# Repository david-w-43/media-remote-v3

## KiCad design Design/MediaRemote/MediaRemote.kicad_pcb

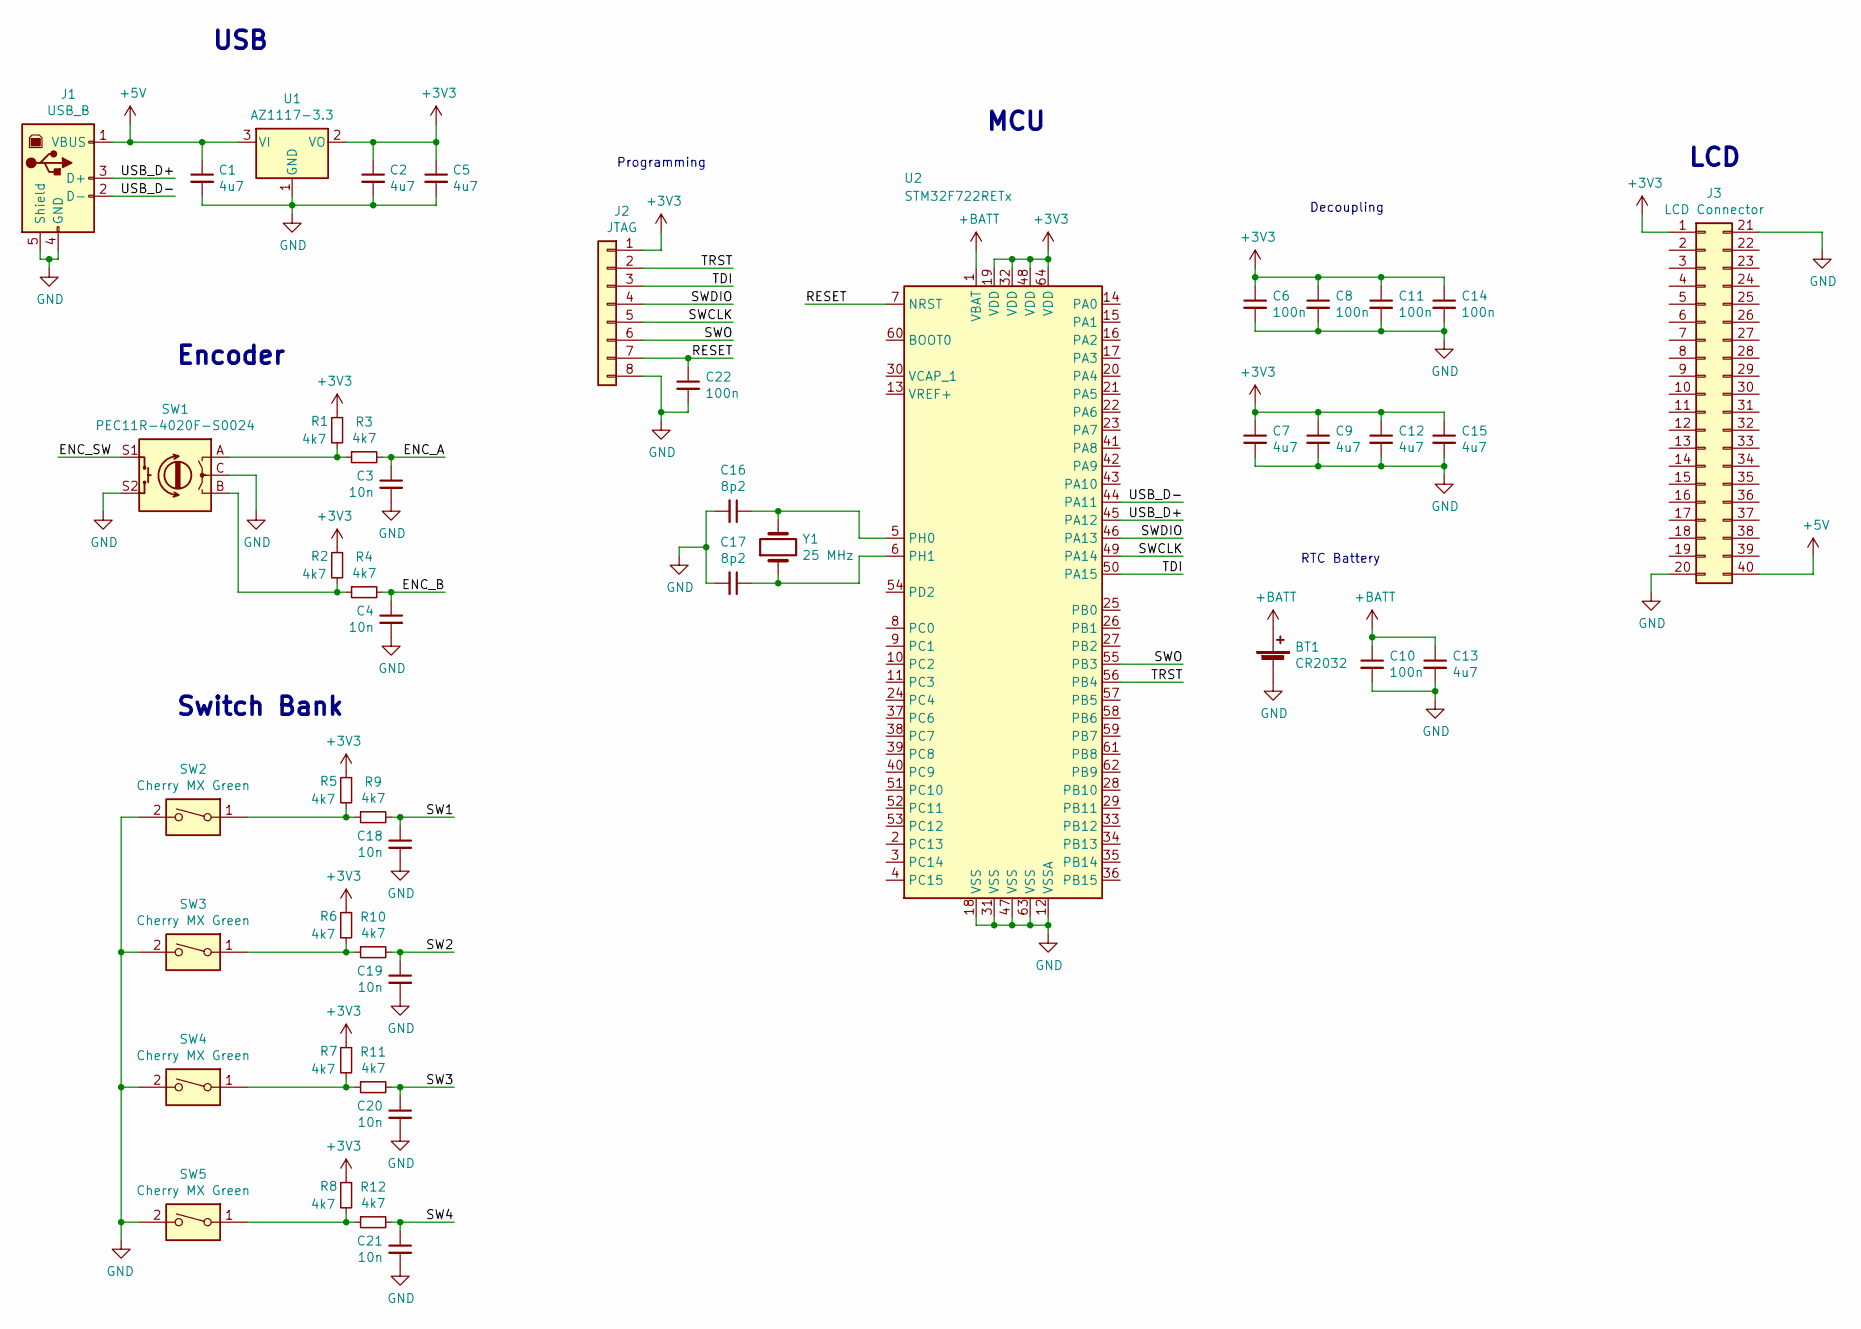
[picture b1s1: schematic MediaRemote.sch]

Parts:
BT1: CR2032; BatteryHolder_Keystone_3002_1x2032
C1, C2, C5, C7, C9, C12, C13, C15: 4u7; C_0805_2012Metric_Pad1.18x1.45mm_HandSolder
C3, C4, C18, C19, C20, C21: 10n; C_0805_2012Metric_Pad1.18x1.45mm_HandSolder
C6, C8, C10, C11, C14, C22: 100n; C_0805_2012Metric_Pad1.18x1.45mm_HandSolder
C16, C17: 8p2; C_0805_2012Metric_Pad1.18x1.45mm_HandSolder
J1: USB_B; USB_B_Lumberg_2411_02_Horizontal
J2: JTAG; PinHeader_1x08_P2.54mm_Vertical
J3: LCD Connector; PinHeader_2x20_P2.54mm_Vertical
R1, R2, R3, R4, R5, R6, R7, R8, R9, R10, R11, R12: 4k7; R_0805_2012Metric_Pad1.20x1.40mm_HandSolder
SW1: PEC11R-4020F-S0024; RotaryEncoder_Alps_EC12E-Switch_Vertical_H20mm
SW2, SW3, SW4, SW5: Cherry MX Green; SW_Cherry_MX_1.00u_Plate
U1: AZ1117-3.3; TO-252-2
U2: STM32F722RETx; LQFP-64_10x10mm_P0.5mm
Y1: 25 MHz; Crystal_HC49-4H_Vertical

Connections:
+3V3: C2.1, C5.1, C6.1, C7.1, C8.1, C9.1, C11.1, C12.1, C14.1, C15.1, J2.1, J3.1, R1.1, R2.1, R5.1, R6.1, R7.1, R8.1, U1.2 (VO), U2.19 (VDD), U2.32 (VDD), U2.48 (VDD), U2.64 (VDD)
+5V: C1.1, J1.1 (VBUS), J3.40, U1.3 (VI)
+BATT: BT1.1 (+), C10.1, C13.1, U2.1 (VBAT)
/ENC_A: C3.1, R3.2
/ENC_B: C4.1, R4.2
/ENC_SW: SW1.S1
/RESET: C22.1, J2.7, U2.7 (NRST)
/SW1: C18.1, R9.2
/SW2: C19.1, R10.2
/SW3: C20.1, R11.2
/SW4: C21.1, R12.2
/SWCLK: J2.5, U2.49 (PA14)
/SWDIO: J2.4, U2.46 (PA13)
/SWO: J2.6, U2.55 (PB3)
/TDI: J2.3, U2.50 (PA15)
/TRST: J2.2, U2.56 (PB4)
/USB_D+: J1.3 (D+), U2.45 (PA12)
/USB_D-: J1.2 (D-), U2.44 (PA11)
GND: BT1.2 (-), C1.2, C2.2, C3.2, C4.2, C5.2, C6.2, C7.2, C8.2, C9.2, C10.2, C11.2, C12.2, C13.2, C14.2, C15.2, C16.2, C17.2, C18.2, C19.2, C20.2, C21.2, C22.2, J1.4 (GND), J1.5 (Shield), J2.8, J3.20, J3.21, SW1.C, SW1.S2, SW2.2, SW3.2, SW4.2, SW5.2, U1.1 (GND), U2.12 (VSSA), U2.18 (VSS), U2.31 (VSS), U2.47 (VSS), U2.63 (VSS)
unnamed: C16.1, U2.5 (PH0), Y1.2
unnamed: C17.1, U2.6 (PH1), Y1.1
unnamed: R1.2, R3.1, SW1.A
unnamed: R2.2, R4.1, SW1.B
unnamed: R5.2, R9.1, SW2.1
unnamed: R6.2, R10.1, SW3.1
unnamed: R7.2, R11.1, SW4.1
unnamed: R8.2, R12.1, SW5.1

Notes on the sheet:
Switch Bank
MCU
Encoder
LCD
Decoupling
RTC Battery
Programming
USB

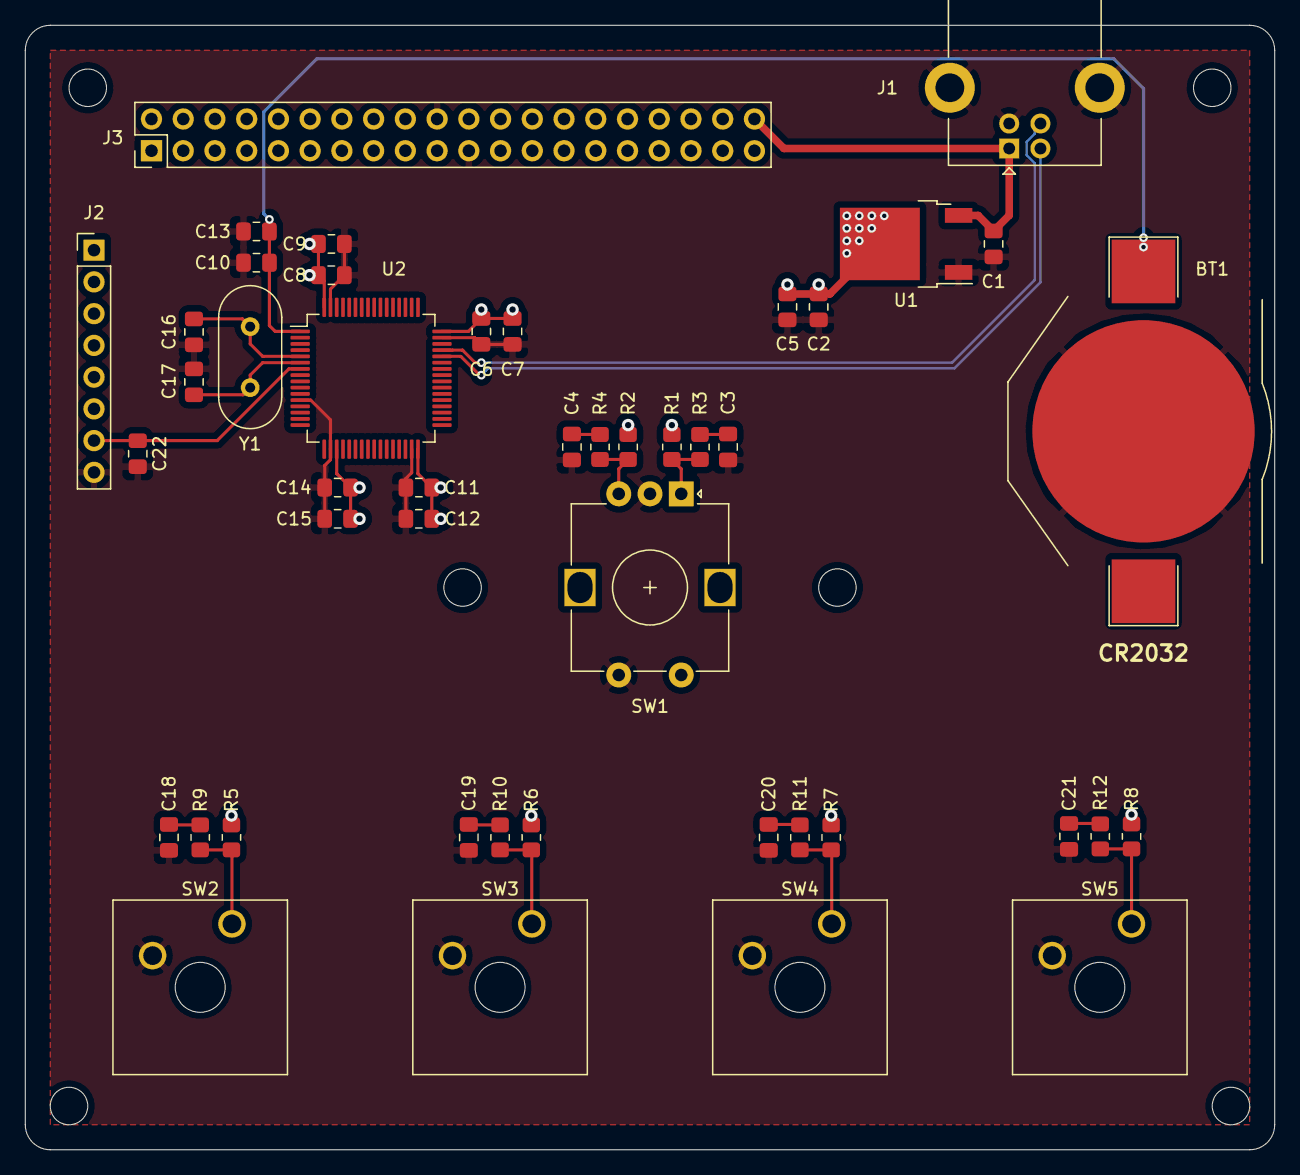
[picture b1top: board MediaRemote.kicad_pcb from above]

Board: 2 copper layers, 100.0 x 90.0 mm, 46 parts (0 on the bottom side), 26 nets.

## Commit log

2021-07-26 Add .gitignore and .gitattributes.
2021-07-26 Add project files.
2021-07-27 Demonstrates Media Application Interface with MEF
2021-07-27 Some basic serial comms methods
2021-07-29 Moved CompanionApplication to new folder, added STM32Cube project
2021-08-02 Added tray icon
2021-08-03 Implemented timer and events to monitor changes
2021-08-04 Release COM object on disconnect
2021-08-04 iTunes member implementations
2021-08-04 Automatically load interfaces into tray icon context menu
2021-08-06 Sets application interface with context menu
2021-08-06 Update .gitattributes
    Exclude stm32 drivers from language stats
2021-08-06 Added classes and assembly for future Discord RP support
2021-08-21 Fixed getting current time
2021-09-27 Added KiCAD project
2021-09-27 Updated PCB
2021-12-04 Added command handler, remote connection interface, and started to implement command formatting
2021-12-04 Renamings, added unit test assembly
2021-12-04 Added unit test compatibility
